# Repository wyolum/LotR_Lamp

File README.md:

# LotR_Lamp
3D printed Lord of the Rings inspired table / desk lamp.
Derived from jerome95's LotR Lamp on Instructables at https://www.instructables.com/Lord-of-the-Rings-Lamp/

I've completely redesigned this from the ground up in FreeCAD

## 3D Printed Parts
- BASE : Lamp base, which houses the micro-controller and a barrel socket adapter. Single color in black. Supports are optional (depending on how good the printer is). There are 4 holes for M3 screws. The 4 screws can act as feet, and if wired to the micro-controller, can be used as 4 touch pads to act as buttons. The buttons can then be used to cycle through different animations, or adjust LED intensity etc.
- BASE COVER : 2 color printing. The cover is black, and the embossed text and tree are white
- PILLAR LEFT and RIGHT : Vertical support pillars in two parts for easier printing and assembly. There is a channel for the wires from micro-controller to LED ring. There are a pair of 1.9 mm holes through which you can insert 1.75 mm filament to staple the top part of the two halves of the vertical pillars. The bottom of the pillars have screw fixing holes. Insert pillars through the Base Cover, and then insert the pillars in the Base. Finally, use 4 wood screws / self tapping screws to nicely hold it all together.
- RING COVER : This is the bottom part of the main ring, and is printed in GOLD / COPPER or similar filament.
- RING : This requires 2 color printing. The inner part of the shell and the text is in white / translucent, and the outer shell is in GOLD / COPPER.

## ELECTRONICS
- LED ring, with 64 addressable LEDs, WS2812 or similar.
- Micro-controller : I used Arduino Nano, but any controller will do the job.
- Example code is in the CODE sub folder

## RENDERS

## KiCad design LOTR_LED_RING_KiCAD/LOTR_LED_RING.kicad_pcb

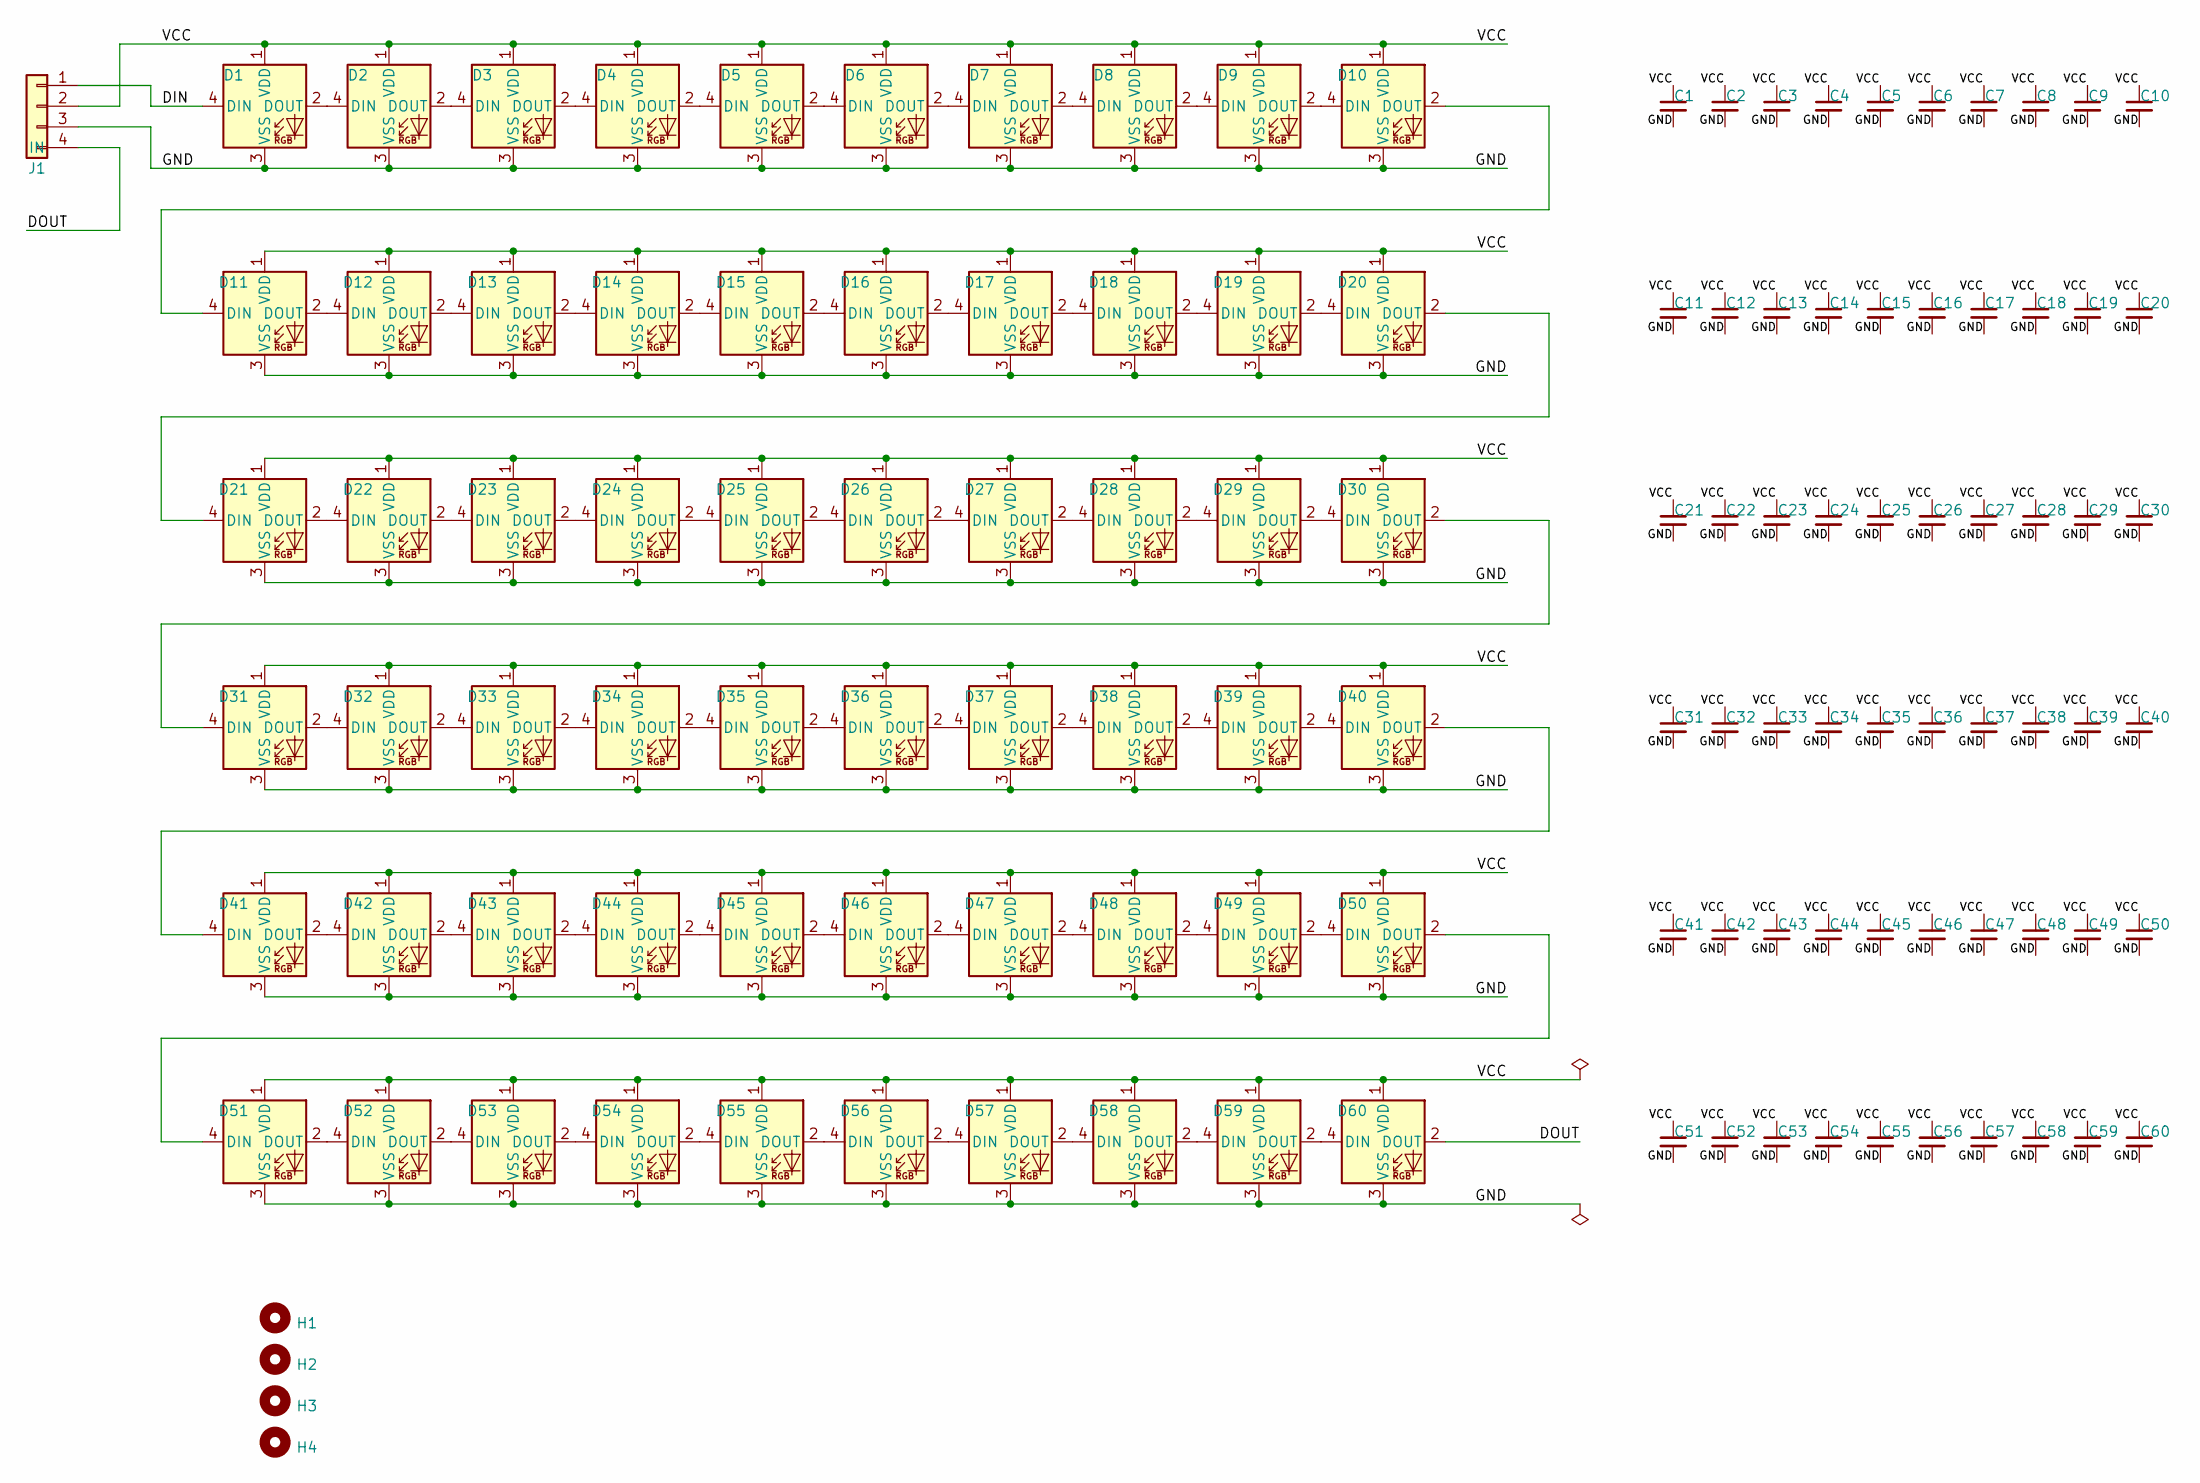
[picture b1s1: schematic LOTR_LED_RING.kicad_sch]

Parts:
C1, C2, C3, C4, C5, C6, C7, C8, C9, C10, C11, C12, C13, C14, C15, C16, C17, C18, C19, C20, C21, C22, C23, C24, C25, C26, C27, C28, C29, C30, C31, C32, C33, C34, C35, C36, C37, C38, C39, C40, C41, C42, C43, C44, C45, C46, C47, C48, C49, C50, C51, C52, C53, C54, C55, C56, C57, C58, C59, C60: 100nF; C_0402_1005Metric
D1, D2, D3, D4, D5, D6, D7, D8, D9, D10, D11, D12, D13, D14, D15, D16, D17, D18, D19, D20, D21, D22, D23, D24, D25, D26, D27, D28, D29, D30, D31, D32, D33, D34, D35, D36, D37, D38, D39, D40, D41, D42, D43, D44, D45, D46, D47, D48, D49, D50, D51, D52, D53, D54, D55, D56, D57, D58, D59, D60: WS2812B; LED_WS2812B_PLCC4_5.0x5.0mm_P3.2mm
H1, H2, H3, H4: MountingHole; MountingHole_1.27mm
J1: IN; PinHeader_1x04_P1.27mm_Vertical_SMD_Pin1Left

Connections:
/DIN: D1.4 (DIN), J1.1
/DOUT: D60.2 (DOUT), J1.4
/GND: C1.2, C2.2, C3.2, C4.2, C5.2, C6.2, C7.2, C8.2, C9.2, C10.2, C11.2, C12.2, C13.2, C14.2, C15.2, C16.2, C17.2, C18.2, C19.2, C20.2, C21.2, C22.2, C23.2, C24.2, C25.2, C26.2, C27.2, C28.2, C29.2, C30.2, C31.2, C32.2, C33.2, C34.2, C35.2, C36.2, C37.2, C38.2, C39.2, C40.2, C41.2, C42.2, C43.2, C44.2, C45.2, C46.2, C47.2, C48.2, C49.2, C50.2, C51.2, C52.2, C53.2, C54.2, C55.2, C56.2, C57.2, C58.2, C59.2, C60.2, D1.3 (VSS), D2.3 (VSS), D3.3 (VSS), D4.3 (VSS), D5.3 (VSS), D6.3 (VSS), D7.3 (VSS), D8.3 (VSS), D9.3 (VSS), D10.3 (VSS), D11.3 (VSS), D12.3 (VSS), D13.3 (VSS), D14.3 (VSS), D15.3 (VSS), D16.3 (VSS), D17.3 (VSS), D18.3 (VSS), D19.3 (VSS), D20.3 (VSS), D21.3 (VSS), D22.3 (VSS), D23.3 (VSS), D24.3 (VSS), D25.3 (VSS), D26.3 (VSS), D27.3 (VSS), D28.3 (VSS), D29.3 (VSS), D30.3 (VSS), D31.3 (VSS), D32.3 (VSS), D33.3 (VSS), D34.3 (VSS), D35.3 (VSS), D36.3 (VSS), D37.3 (VSS), D38.3 (VSS), D39.3 (VSS), D40.3 (VSS), D41.3 (VSS), D42.3 (VSS), D43.3 (VSS), D44.3 (VSS), D45.3 (VSS), D46.3 (VSS), D47.3 (VSS), D48.3 (VSS), D49.3 (VSS), D50.3 (VSS), D51.3 (VSS), D52.3 (VSS), D53.3 (VSS), D54.3 (VSS), D55.3 (VSS), D56.3 (VSS), D57.3 (VSS), D58.3 (VSS), D59.3 (VSS), D60.3 (VSS), J1.3
/VCC: C1.1, C2.1, C3.1, C4.1, C5.1, C6.1, C7.1, C8.1, C9.1, C10.1, C11.1, C12.1, C13.1, C14.1, C15.1, C16.1, C17.1, C18.1, C19.1, C20.1, C21.1, C22.1, C23.1, C24.1, C25.1, C26.1, C27.1, C28.1, C29.1, C30.1, C31.1, C32.1, C33.1, C34.1, C35.1, C36.1, C37.1, C38.1, C39.1, C40.1, C41.1, C42.1, C43.1, C44.1, C45.1, C46.1, C47.1, C48.1, C49.1, C50.1, C51.1, C52.1, C53.1, C54.1, C55.1, C56.1, C57.1, C58.1, C59.1, C60.1, D1.1 (VDD), D2.1 (VDD), D3.1 (VDD), D4.1 (VDD), D5.1 (VDD), D6.1 (VDD), D7.1 (VDD), D8.1 (VDD), D9.1 (VDD), D10.1 (VDD), D11.1 (VDD), D12.1 (VDD), D13.1 (VDD), D14.1 (VDD), D15.1 (VDD), D16.1 (VDD), D17.1 (VDD), D18.1 (VDD), D19.1 (VDD), D20.1 (VDD), D21.1 (VDD), D22.1 (VDD), D23.1 (VDD), D24.1 (VDD), D25.1 (VDD), D26.1 (VDD), D27.1 (VDD), D28.1 (VDD), D29.1 (VDD), D30.1 (VDD), D31.1 (VDD), D32.1 (VDD), D33.1 (VDD), D34.1 (VDD), D35.1 (VDD), D36.1 (VDD), D37.1 (VDD), D38.1 (VDD), D39.1 (VDD), D40.1 (VDD), D41.1 (VDD), D42.1 (VDD), D43.1 (VDD), D44.1 (VDD), D45.1 (VDD), D46.1 (VDD), D47.1 (VDD), D48.1 (VDD), D49.1 (VDD), D50.1 (VDD), D51.1 (VDD), D52.1 (VDD), D53.1 (VDD), D54.1 (VDD), D55.1 (VDD), D56.1 (VDD), D57.1 (VDD), D58.1 (VDD), D59.1 (VDD), D60.1 (VDD), J1.2
unnamed: D1.2 (DOUT), D2.4 (DIN)
unnamed: D2.2 (DOUT), D3.4 (DIN)
unnamed: D3.2 (DOUT), D4.4 (DIN)
unnamed: D4.2 (DOUT), D5.4 (DIN)
unnamed: D5.2 (DOUT), D6.4 (DIN)
unnamed: D6.2 (DOUT), D7.4 (DIN)
unnamed: D7.2 (DOUT), D8.4 (DIN)
unnamed: D8.2 (DOUT), D9.4 (DIN)
unnamed: D9.2 (DOUT), D10.4 (DIN)
unnamed: D10.2 (DOUT), D11.4 (DIN)
unnamed: D11.2 (DOUT), D12.4 (DIN)
unnamed: D12.2 (DOUT), D13.4 (DIN)
unnamed: D13.2 (DOUT), D14.4 (DIN)
unnamed: D14.2 (DOUT), D15.4 (DIN)
unnamed: D15.2 (DOUT), D16.4 (DIN)
unnamed: D16.2 (DOUT), D17.4 (DIN)
unnamed: D17.2 (DOUT), D18.4 (DIN)
unnamed: D18.2 (DOUT), D19.4 (DIN)
unnamed: D19.2 (DOUT), D20.4 (DIN)
unnamed: D20.2 (DOUT), D21.4 (DIN)
unnamed: D21.2 (DOUT), D22.4 (DIN)
unnamed: D22.2 (DOUT), D23.4 (DIN)
unnamed: D23.2 (DOUT), D24.4 (DIN)
unnamed: D24.2 (DOUT), D25.4 (DIN)
unnamed: D25.2 (DOUT), D26.4 (DIN)
unnamed: D26.2 (DOUT), D27.4 (DIN)
unnamed: D27.2 (DOUT), D28.4 (DIN)
unnamed: D28.2 (DOUT), D29.4 (DIN)
unnamed: D29.2 (DOUT), D30.4 (DIN)
unnamed: D30.2 (DOUT), D31.4 (DIN)
unnamed: D31.2 (DOUT), D32.4 (DIN)
unnamed: D32.2 (DOUT), D33.4 (DIN)
unnamed: D33.2 (DOUT), D34.4 (DIN)
unnamed: D34.2 (DOUT), D35.4 (DIN)
unnamed: D35.2 (DOUT), D36.4 (DIN)
unnamed: D36.2 (DOUT), D37.4 (DIN)
unnamed: D37.2 (DOUT), D38.4 (DIN)
unnamed: D38.2 (DOUT), D39.4 (DIN)
unnamed: D39.2 (DOUT), D40.4 (DIN)
unnamed: D40.2 (DOUT), D41.4 (DIN)
unnamed: D41.2 (DOUT), D42.4 (DIN)
unnamed: D42.2 (DOUT), D43.4 (DIN)
unnamed: D43.2 (DOUT), D44.4 (DIN)
unnamed: D44.2 (DOUT), D45.4 (DIN)
unnamed: D45.2 (DOUT), D46.4 (DIN)
unnamed: D46.2 (DOUT), D47.4 (DIN)
unnamed: D47.2 (DOUT), D48.4 (DIN)
unnamed: D48.2 (DOUT), D49.4 (DIN)
unnamed: D49.2 (DOUT), D50.4 (DIN)
unnamed: D50.2 (DOUT), D51.4 (DIN)
unnamed: D51.2 (DOUT), D52.4 (DIN)
unnamed: D52.2 (DOUT), D53.4 (DIN)
unnamed: D53.2 (DOUT), D54.4 (DIN)
unnamed: D54.2 (DOUT), D55.4 (DIN)
unnamed: D55.2 (DOUT), D56.4 (DIN)
unnamed: D56.2 (DOUT), D57.4 (DIN)
unnamed: D57.2 (DOUT), D58.4 (DIN)
unnamed: D58.2 (DOUT), D59.4 (DIN)
unnamed: D59.2 (DOUT), D60.4 (DIN)

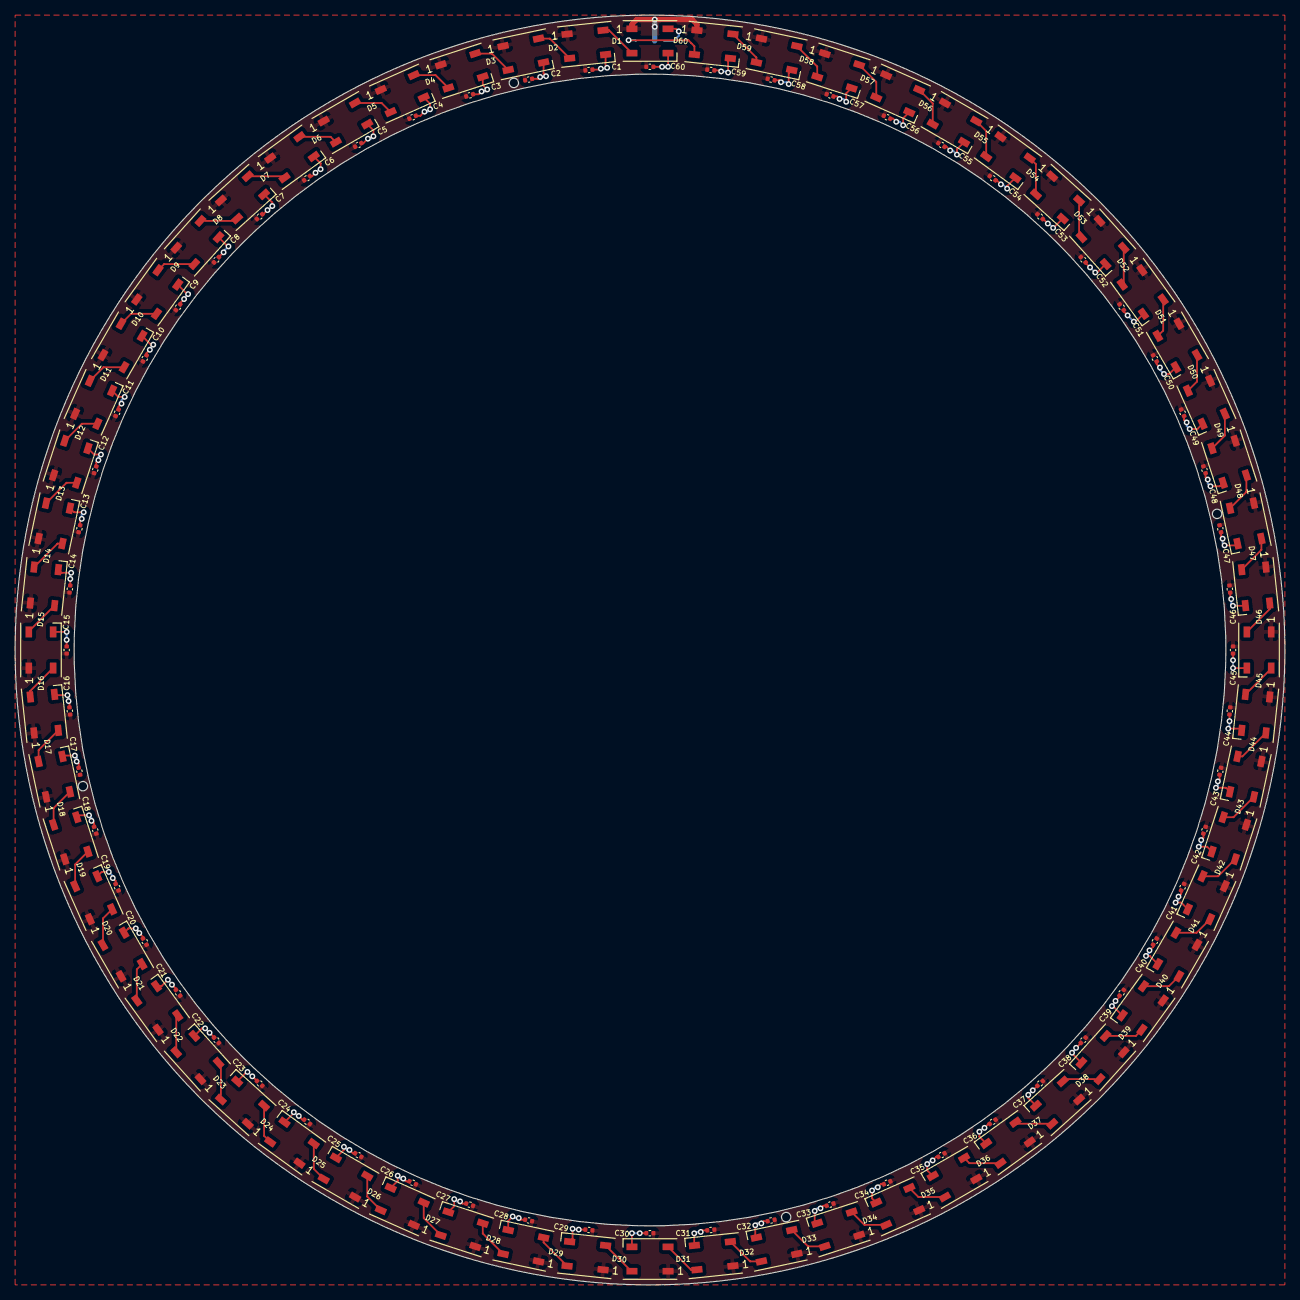
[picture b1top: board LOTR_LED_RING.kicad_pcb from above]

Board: 2 copper layers, 172.0 x 172.0 mm, 121 parts (1 on the bottom side), 63 nets.

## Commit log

2023-04-25 added PDF
2023-04-29 added several versions in fabricate folder
2023-06-15 rebuilt lost files
2023-06-16 modified Ring attachment cylinder
2023-06-16 added cover for LED ring STL
2024-09-29 new base for LoTR ring lamp
2024-10-02 minor mods to new base
2024-11-22 almost final version
